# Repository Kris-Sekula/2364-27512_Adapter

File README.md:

# 2364-27512_Adapter
Adapter to use EPROM as a replacement of PROM, commonly used for Commodore 64 KERNAL replacement. 

I use it with my EPROM Emulator. 

Inspired by SukkoPera/Open2327RomAdapter but with resistors placed on top layer to protect bottom layer from screwdriver that I often use to remove the EPROM from the socket. Added standard 2.54mm header for optional extension of A13-A15 lines, solder pads nicely spaced to allow soldering of extention cable for switchable images.

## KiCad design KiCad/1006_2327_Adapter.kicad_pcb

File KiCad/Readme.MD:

KiCad sources to produce the PCB

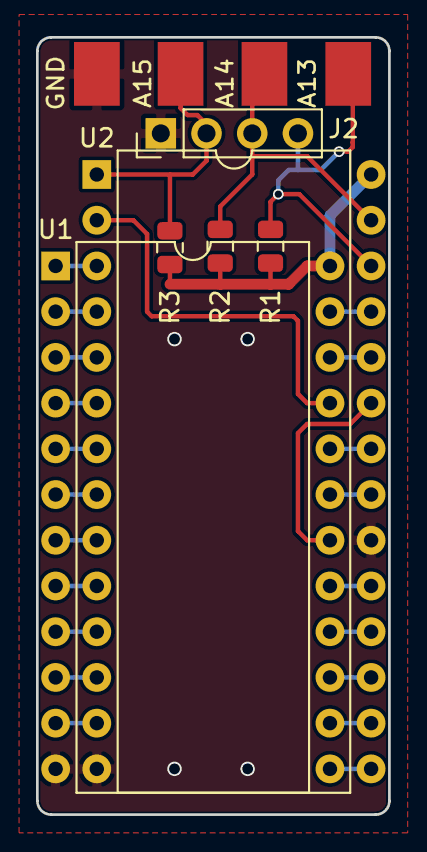
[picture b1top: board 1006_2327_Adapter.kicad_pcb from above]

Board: 2 copper layers, 19.6 x 43.2 mm, 7 parts (0 on the bottom side), 27 nets.

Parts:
J1: Header_SMD; LoosePads-4KS
J2: Header_THT; PinHeader_1x04_P2.54mm_Vertical
R1, R2, R3: 10K; R_0805_2012Metric
U1: 2364; DIP-24_W15.24mm
U2: 27C512; DIP-28_W15.24mm

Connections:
/A0: U1.8, U2.10
/A1: U1.7, U2.9
/A2: U1.6, U2.8
/A3: U1.5, U2.7
/A4: U1.4, U2.6
/A5: U1.3, U2.5
/A6: U1.2, U2.4
/A7: U1.1, U2.3
/A8: U1.23, U2.25
/A9: U1.22, U2.24
/A10: U1.19, U2.21
/A11: U1.18, U2.23
/A12: U1.21, U2.2
/D0: U1.9, U2.11
/D1: U1.10, U2.12
/D2: U1.11, U2.13
/D3: U1.13, U2.15
/D4: U1.14, U2.16
/D5: U1.15, U2.17
/D6: U1.16, U2.18
/D7: U1.17, U2.19
GND: J1.1, J2.1, U1.12, U2.14, U2.20
unnamed: J1.2, J2.2, R3.2, U2.1
unnamed: J1.3, J2.3, R2.2, U2.27
unnamed: J1.4, J2.4, R1.2, U2.26
unnamed: U1.20, U2.22
VCC: R1.1, R2.1, R3.1, U1.24, U2.28
